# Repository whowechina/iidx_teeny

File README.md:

# Teeny IIDX - Beatmania IIDX controller

# IMPORTANT NOTE
After a major refactor, I've merged this "IIDX Teeny" repository into the "IIDX Pico" repository and will no longer update this repository. Please refer to the "IIDX Pico" repository for guides and the latest updates.

https://github.com/whowechina/iidx_pico

This is the a small brother of my previous Pico IIDX controller. Both Pico IIDX and this Teeny IIDX share the same firmware which is in Pico IIDX repo.
<https://github.com/whowechina/iidx_pico>

Here's me playing Konami's Beatmania IIDX ultimate mobile with it. Yes, I'm a cat lover.
https://github.com/whowechina/iidx_teeny/assets/11623830/5aea28e7-6961-4d22-b5de-0fad74cdeacf

Features:
* It's thin, really really thin and foldable.
* HID lights, of course!
* Multiple turntable effects.
* Many live settings.
* All source files open.
* It's easier and more portable than IIDX Pico.

Thanks to many respectful guys/companies who made their tools or materials free or open source (KiCad, OpenSCAD, InkScape, Raspberry things). And also:
* RP_Silicon_KiCad: https://github.com/HeadBoffin/RP_Silicon_KiCad
* Switch_Keyboard_Kailh: https://github.com/kiswitch/keyswitch-kicad-library
* Type-C: https://github.com/ai03-2725/Type-C.pretty

## Notes
This project heavily relies on 3D printing, and skills to solder tiny components and thin cables.

## My Other Projects
You can check out my other cool projects.

* Popn Pico: https://github.com/whowechina/popn_pico
* IIDX Pico: https://github.com/whowechina/iidx_pico
* IIDX Teeny: https://github.com/whowechina/iidx_teeny
* Chu Pico: https://github.com/whowechina/chu_pico
* Mai Pico: https://github.com/whowechina/mai_pico
* Diva Pico: https://github.com/whowechina/diva_pico
* AIC Pico: https://github.com/whowechina/aic_pico
* Groove Pico: https://github.com/whowechina/groove_pico
* Geki Pico: https://github.com/whowechina/geki_pico
* Musec Pico: https://github.com/whowechina/musec_pico

## **Disclaimer** ##
I made this project in my personal time with no financial benefit or sponsorship. I will continue to improve the project. I have done my best to ensure that everything is accurate and functional, there's always a chance that mistakes may occur. I cannot be held responsible for any loss of your time or money that may result from using this open source project. Thank you for your understanding.

## About the License
It's CC-NC. So DIY for yourself and for your friend, don't make money from it. And plagiarism that doesn’t even dare to mention the original author is not acceptable. Plase note that pooling orders and group buying for raw materials is acceptable. Selling off any leftover components without profit is also acceptable.

If you're interested in some kind of commercial use, please contact me (Discord, QQ group, Wechat group or leave your contact in issue section).

## My Discord Invitation
https://discord.gg/M8f2PPQFEA

## HOW TO BUILD
### Turntable Materials
* 1x AS5600 hall angular sensor board set (23mm\*23mm)  
  
* 1x 6mm\*2mm magnet (must be radially magnetized), normally comes with the AS5600 board set, you can use one with different size of course, but you need to modify the 3D file.
* 1x 61804-2RS deep groove ball bearing (20x32x7mm), normally < 5US$;
* 1x WS2812B LED ring board, or RGB LED strip (recommended). Choose ones with dense LED arrangement (better if >=24 LEDs per board, or >90 LEDS per meter for LED strip);
* 6x M3*6mm screws (large flat head is better) and hex nuts.
* Non slip self-adhesive silicon pads (7-8mm diameter, also for Keyboard).  

### Keyboard Materials
* 1x Raspberry Pi Pico or Pi Pico W (if you need Bluetooth support).  
  https://www.raspberrypi.com/products/raspberry-pi-pico
* 7x Kailh Choc v1 key switches, to get better play feel, 7 of them should be linear (35gf to 50gf).  
  https://www.kailhswitch.com/mechanical-keyboard-switches/low-profile-key-switches/burnt-orange-switch.html  
* 6x Panasonic 6mm square tactile switch EVQP1K05M or a similar Alps one.  
  https://www3.panasonic.biz/ac/e/dl/catalog/index.jsp?series_cd=3473&part_no=EVQP1K05M
* 1x USB Type-C socket (918-418K2023S40001 or KH-TYPE-C-16P)
* 18x WS2812B-3528 RGB LEDs to light up the keys.
* 2x 0603 5.1kohm resistors for USB, (R20, R21).
* 2x 0603 0~20ohm resistors for light signals (R1, R2).
* 2x 0603 1-10kohm resistors for I2C pullup (R3, R4).
* 5x 0805 or 0603, 0.1 to 1uF capacitors.
* 4x M3*6mm screws and hex nuts to fix parts together.

### Connection for Foldable
* 2x silicon shielded cables with 4 core cables (about 25cm each), one for the RGB LEDs and one for the sensor.
* 1x silicon tube, outer diameter 27mm, inner diameter 25mm, so the wall thickness is 1mm.

### Step 1 - Buy
* Keyboard PCB  
  Just go [JLC](https://jlcpcb.com/) and make the order. Make sure the board thickness is **1.2mm**, it's very very important!

### Step 2 - 3D Print
#### Keyboard
Print with PLA transparent materials, 0.2mm layer, 4 walls, using 0.4mm nozzle.
* PCB bottom (teeny_bottom_P1|P2.stl, choose one according to your 1P or 2P choice).
* PCB top (teeny_top.stl)  
  Bambu Lab's AMS system is highly recommended, use PLA black for 3.0mm+ layers. So you'll have cool looking logo and key frames.

#### Turntable 
Again, print with 0.2mm layer, using 0.4mm nozzle, 5 walls. "Seam Position" should be set to "**Random**" in your slicer, not only it looks better, it makes the bearing-flange coupling smoother and tension distributed more evenly.  

* Base (teeny_tt.stl), PLA transparent.
* Bearing seat (teeny_bearing.stl), 20-60% fill, PLA white.
* Flange for disc (teeny_shaft.stl), 60% fill, PLA white.
* The disc (teeny_disc.stl), 60% fill, all fill patterns should be set to "Concentric".

#### Button keycaps  
* Print upside down, with easy-to-remove support materials.  

### Other Steps
It's similar to my previous Pico IIDX project, just read the documentation there.
<https://github.com/whowechina/iidx_pico>

But there're something you need to pay attention:
* On Teeny's PCB, there are 2 sets of soldering pads, 1 set is for AS5600, the other is for the WS2812 LED ring.
  * J1 is for LED, 5V is the power, L is LED signal, G is ground.
  * J2 is for AS5600, 3V is the power (actually 3.3V), S is I2C SCL, D is I2C SDA, G is ground.
  
  * Please use two seperate cables to wire LED and AS5600, both (or at least one) should be shielded to prevent crosstalk interference.
  * Choose thin/soft cables, so they can fit. Get ultra thin USB cable or extract daughter cables from abandoned HDMI cables. 2mm diameter is the best.
  * R3, R4 are optional, if turntable (I2C) is not working properly, you may try use them.
  * There's a nice manual in IIDX Pico's repo, under doc folder. Follow the manual to set AS5600 to I2C mode and then do your LED ring setup.  
  <https://github.com/whowechina/iidx_pico/tree/main/doc/Firmware_manual.pdf>

#### About the License
It's CC-NC. So diy for yourself and for your friend, don't make money from it.

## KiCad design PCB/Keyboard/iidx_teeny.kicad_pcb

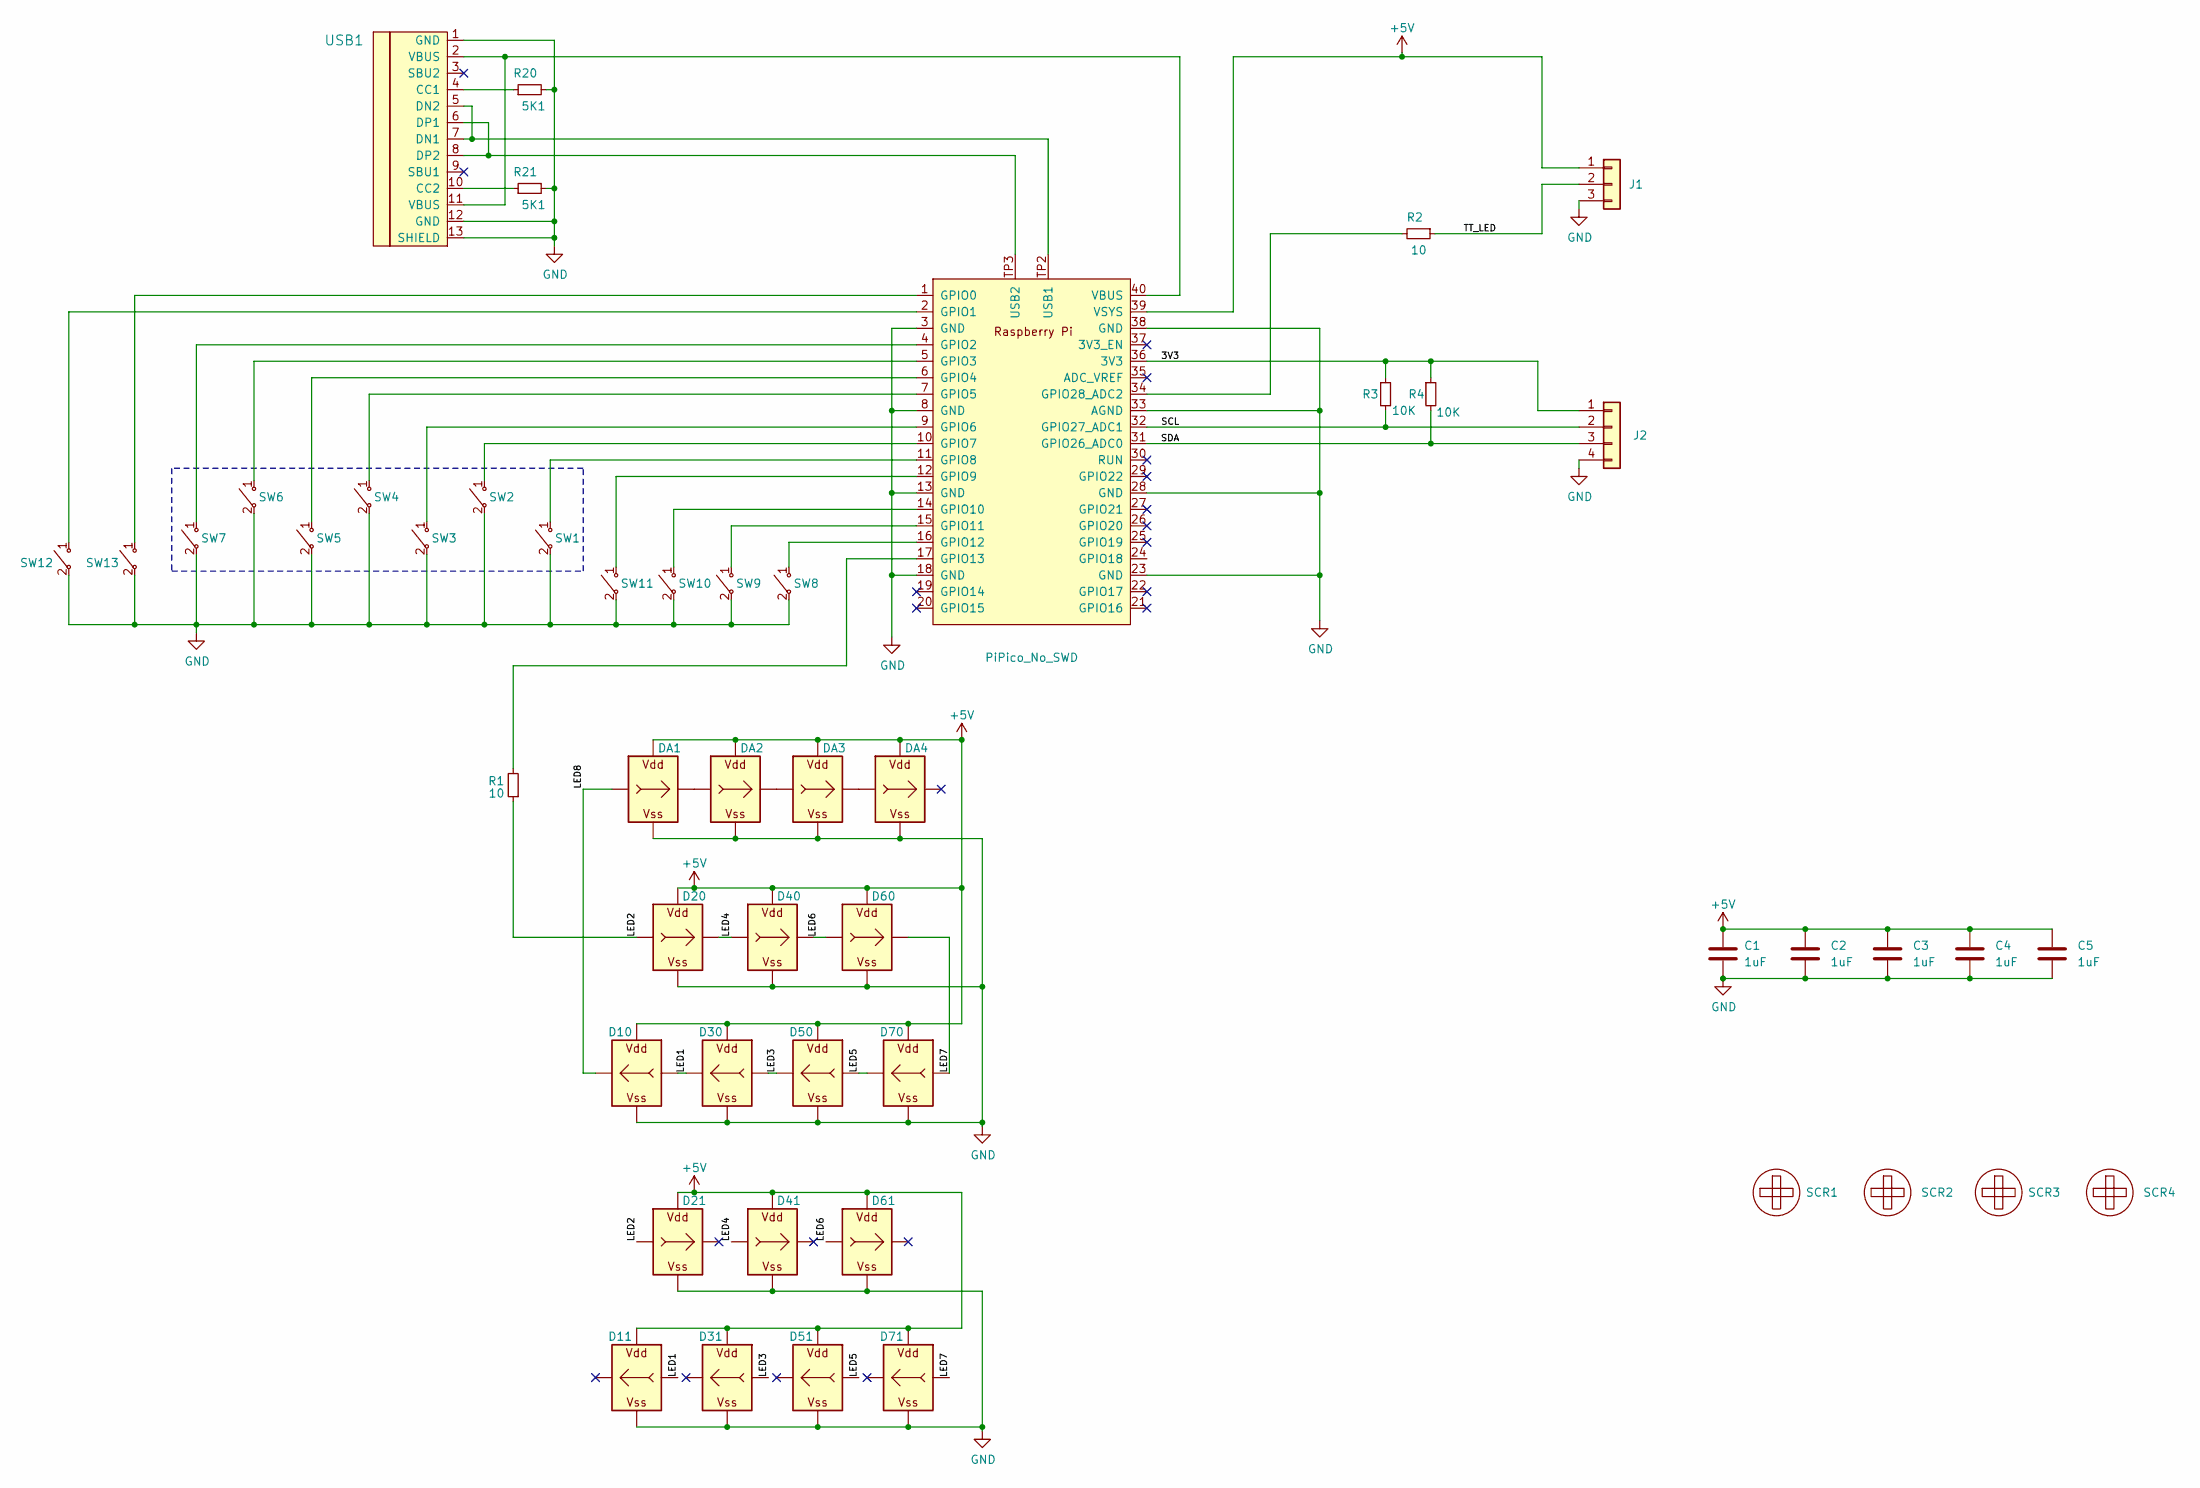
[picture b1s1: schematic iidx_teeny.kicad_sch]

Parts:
C1, C2, C3, C4, C5: 1uF; C_0805_2012Metric
D10, D11, D20, D21, D30, D31, D40, D41, D50, D51, D60, D61, D70, D71: WS2812B_Unified; WS2812B-2835
DA1, DA2, DA3, DA4: WS2812B_Unified; WS2812B-2835
J1: Conn_01x03; Solder_3P
J2: Conn_01x04; Solder_4P
R1, R2: 10; R_0603_1608Metric_Pad0.98x0.95mm_HandSolder; LCSC C23186
R3, R4: 10K; R_0603_1608Metric_Pad0.98x0.95mm_HandSolder; LCSC C23186
R20, R21: 5K1; R_0603_1608Metric_Pad0.98x0.95mm_HandSolder; LCSC C23186
SCR1, SCR2, SCR3, SCR4: ScrewHole; MountingHole_3.2mm_M3
SW1, SW2, SW3, SW4, SW5, SW6, SW7: SWITCH_SPST; SW_Kailh_Choc_V1V2_1.00u_LED
SW8, SW9, SW10, SW11, SW12, SW13: SWITCH_SPST; EVQP1K05M
U1: PiPico_No_SWD; RPi_Pico_SMD_Pins_No_SWD_No_Text
USB1: U262-161N-4BVC11; HRO-TYPE-C-31-M-12-Assembly; LCSC C319148

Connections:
+5V: C1.1, C2.1, C3.1, C4.1, C5.1, D10.V (VDD), D11.V (VDD), D20.V (VDD), D21.V (VDD), D30.V (VDD), D31.V (VDD), D40.V (VDD), D41.V (VDD), D50.V (VDD), D51.V (VDD), D60.V (VDD), D61.V (VDD), D70.V (VDD), D71.V (VDD), DA1.V (VDD), DA2.V (VDD), DA3.V (VDD), DA4.V (VDD), J1.1, U1.39 (VSYS)
/3V3: J2.1, R3.1, R4.1, U1.36 (3V3)
/LED1: D10.I (In), D11.I (In), D30.O (Out)
/LED2: D20.I (In), D21.I (In), R1.1
/LED3: D30.I (In), D31.I (In), D50.O (Out)
/LED4: D20.O (Out), D40.I (In), D41.I (In)
/LED5: D50.I (In), D51.I (In), D70.O (Out)
/LED6: D40.O (Out), D60.I (In), D61.I (In)
/LED7: D60.O (Out), D70.I (In), D71.I (In)
/LED8: D10.O (Out), DA1.I (In)
/SCL: J2.2, R3.2, U1.32 (GPIO27_ADC1)
/SDA: J2.3, R4.2, U1.31 (GPIO26_ADC0)
/TT_LED: J1.2, R2.1
GND: C1.2, C2.2, C3.2, C4.2, C5.2, D10.G (VSS), D11.G (VSS), D20.G (VSS), D21.G (VSS), D30.G (VSS), D31.G (VSS), D40.G (VSS), D41.G (VSS), D50.G (VSS), D51.G (VSS), D60.G (VSS), D61.G (VSS), D70.G (VSS), D71.G (VSS), DA1.G (VSS), DA2.G (VSS), DA3.G (VSS), DA4.G (VSS), J1.3, J2.4, R20.2, R21.2, SW1.2 ("~"), SW2.2 ("~"), SW3.2 ("~"), SW4.2 ("~"), SW5.2 ("~"), SW6.2 ("~"), SW7.2 ("~"), SW8.2 ("~"), SW9.2 ("~"), SW10.2 ("~"), SW11.2 ("~"), SW12.2 ("~"), SW13.2 ("~"), U1.3 (GND), U1.8 (GND), U1.13 (GND), U1.18 (GND), U1.23 (GND), U1.28 (GND), U1.33 (AGND), U1.38 (GND), USB1.1 (GND), USB1.12 (GND), USB1.13 (SHIELD)
unnamed: DA1.O (Out), DA2.I (In)
unnamed: DA2.O (Out), DA3.I (In)
unnamed: DA3.O (Out), DA4.I (In)
unnamed: SW13.1 ("~"), U1.1 (GPIO0)
unnamed: SW12.1 ("~"), U1.2 (GPIO1)
unnamed: SW7.1 ("~"), U1.4 (GPIO2)
unnamed: SW6.1 ("~"), U1.5 (GPIO3)
unnamed: SW5.1 ("~"), U1.6 (GPIO4)
unnamed: SW4.1 ("~"), U1.7 (GPIO5)
unnamed: SW3.1 ("~"), U1.9 (GPIO6)
unnamed: SW2.1 ("~"), U1.10 (GPIO7)
unnamed: SW1.1 ("~"), U1.11 (GPIO8)
unnamed: SW11.1 ("~"), U1.12 (GPIO9)
unnamed: SW10.1 ("~"), U1.14 (GPIO10)
unnamed: SW9.1 ("~"), U1.15 (GPIO11)
unnamed: SW8.1 ("~"), U1.16 (GPIO12)
unnamed: R1.2, U1.17 (GPIO13)
unnamed: R2.2, U1.34 (GPIO28_ADC2)
unnamed: U1.TP2 (USB1), USB1.5 (DN2), USB1.7 (DN1)
unnamed: U1.TP3 (USB2), USB1.6 (DP1), USB1.8 (DP2)
unnamed: U1.40 (VBUS), USB1.2 (VBUS), USB1.11 (VBUS)
unnamed: R20.1, USB1.4 (CC1)
unnamed: R21.1, USB1.10 (CC2)

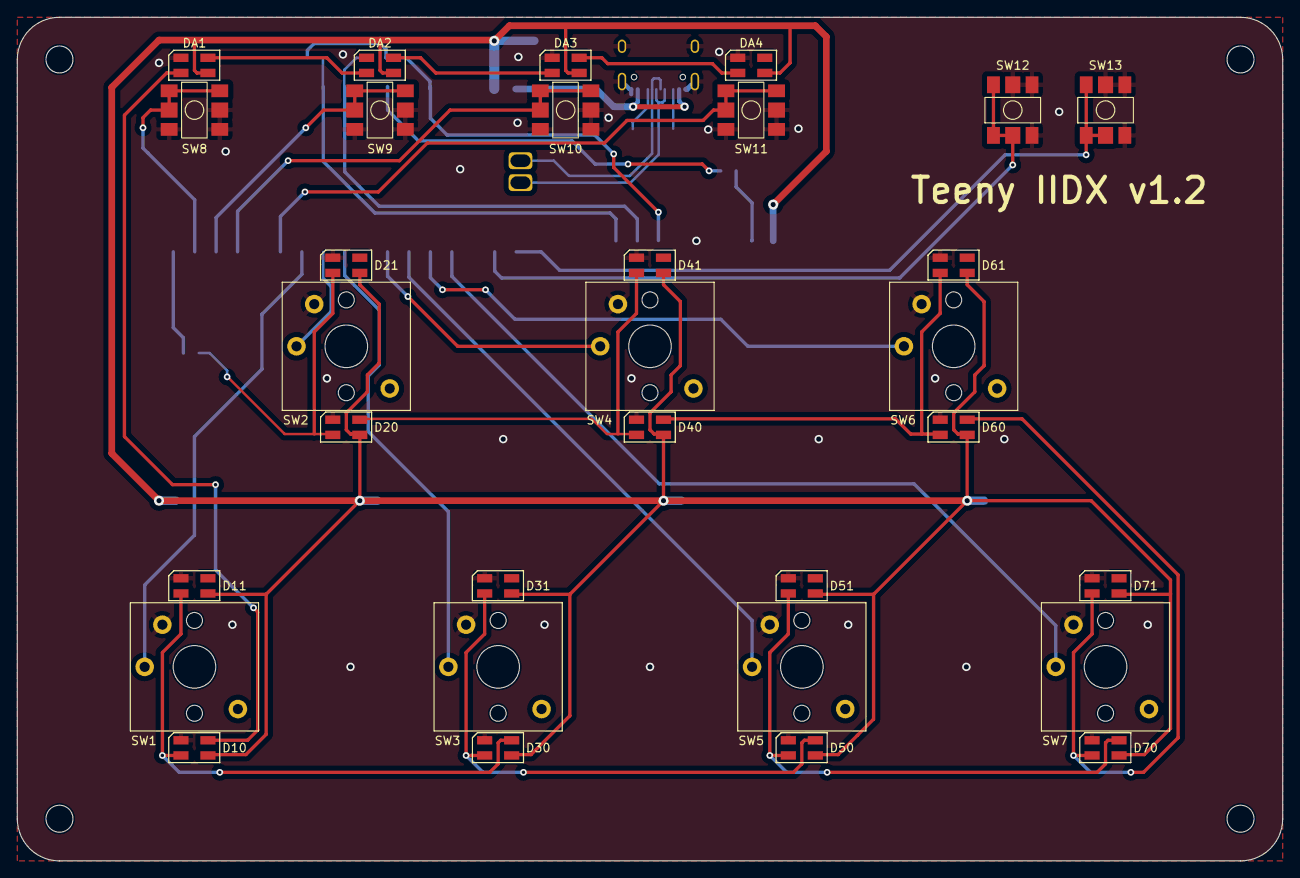
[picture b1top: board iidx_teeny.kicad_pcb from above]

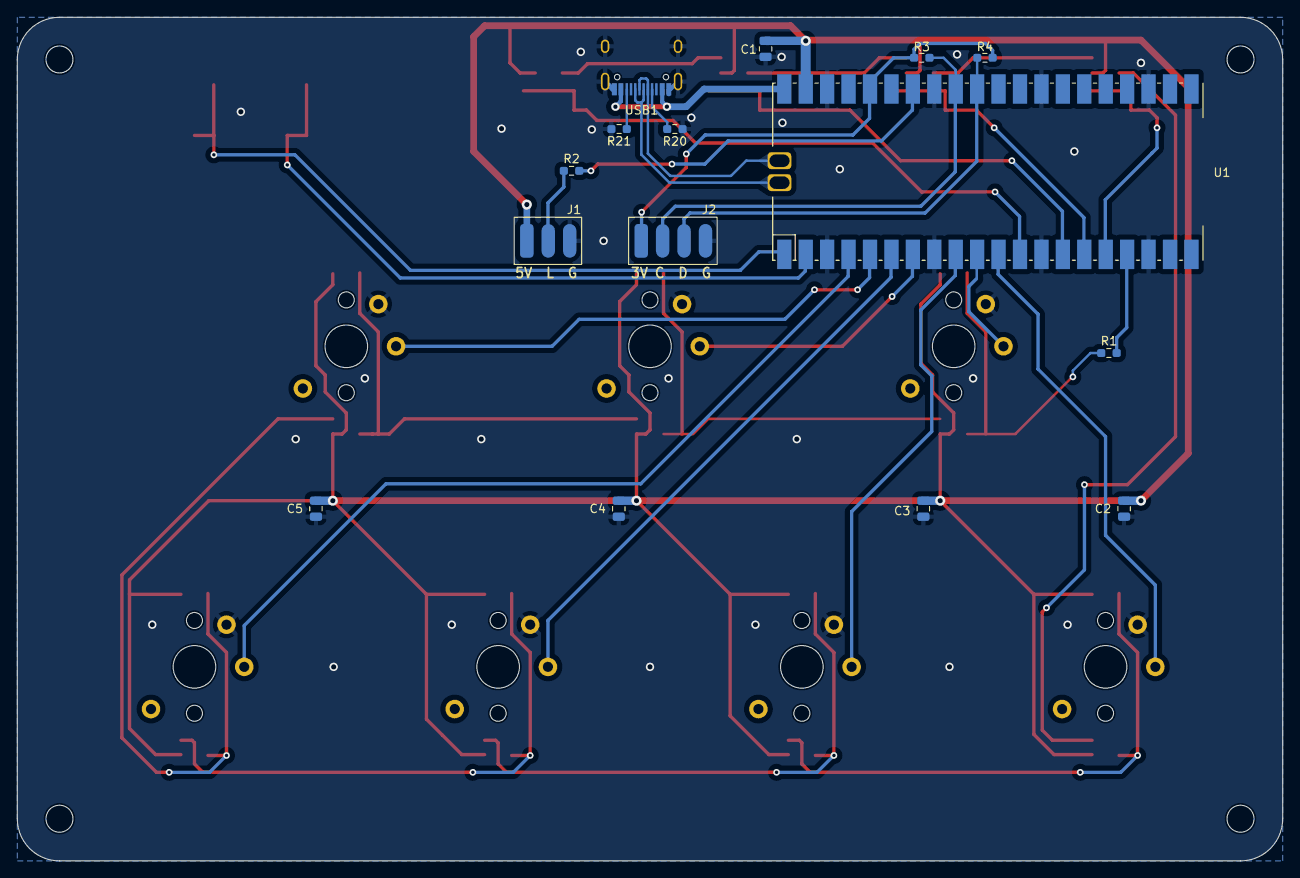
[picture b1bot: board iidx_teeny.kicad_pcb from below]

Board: 2 copper layers, 150.0 x 100.0 mm, 50 parts (15 on the bottom side), 37 nets.

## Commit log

2023-05-01 Cloned from pico iidx
2023-05-01 Finished schematics and board shape
2023-05-03 PCB and keyboard housing done
2023-05-05 Start TT modeling
2023-05-08 Fix top aux hole clearance issue
2023-05-09 Finetune bottom
2023-05-10 Finetune teeny top
2023-05-11 PCB updated with two LEDs per button and larger Y gap
2023-05-11 Keycap updated, works well
2023-05-14 Cad files update (working)
2023-05-21 3D files update to fit v1 PCB
2023-05-21 Put license file
2023-05-26 Better aux and set button frame
2023-05-28 V1 validated, v0 removed
2023-05-31 Documentation update
2023-06-01 Update video
2023-06-02 Update video asset format
2023-06-02 Another try on video format
2023-06-02 Video in README should work now
2023-06-03 Better video cut
2023-07-23 Finetuned hinge cover
2023-10-02 Doc update based on DIYer's feedback
2023-10-14 Crossreference to Mai Pico
2023-12-03 Upload the missing P2 bottom stl file
2023-12-10 Fix minor BOM issue
2023-12-10 Manual gif in README
2024-02-12 Update USB-C position for stable cable connection
2024-09-05 Thanks to some projects
2024-10-02 Update license part in README
2024-10-02 Cross-reference update
2024-10-18 Cross-reference and Discord invitation
2024-10-28 PCB v1.2, easier soldering
2024-11-20 PCB v1.3 (sensors on board)
2024-11-20 Mention 1.2mm in gerber filename
2024-12-13 Claim end of this repo in README
2024-12-18 Freeze this repository with latest files
2024-12-21 Use hex nut to fix disc seat and magnet seat
2025-01-15 Upload missing teeny disc STL
